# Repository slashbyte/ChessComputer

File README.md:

# PI Chess Computer
Modeled after the "Chess Challenger" made in 1978.
This PI powered, retro themed build,
is an open source hardware design capable of running an up to date chess engine, Stockfish.

## Raspberry PI Image Release
[Chess Challenger PI Image](https://github.com/slashbyte/ChessComputer-Source/releases)

### Computer Chess Clubs, BEWARE!
(Thats still a thing, right?)

## Authors
* **Slash/Byte** (slashqpbyte@gmail.com)
## License
This project is licensed under the MIT License
(https://opensource.org/licenses/MIT)
## Acknowledgments
* Science
* Adafruit
* Ponoko (Great fab house)
* Digikey

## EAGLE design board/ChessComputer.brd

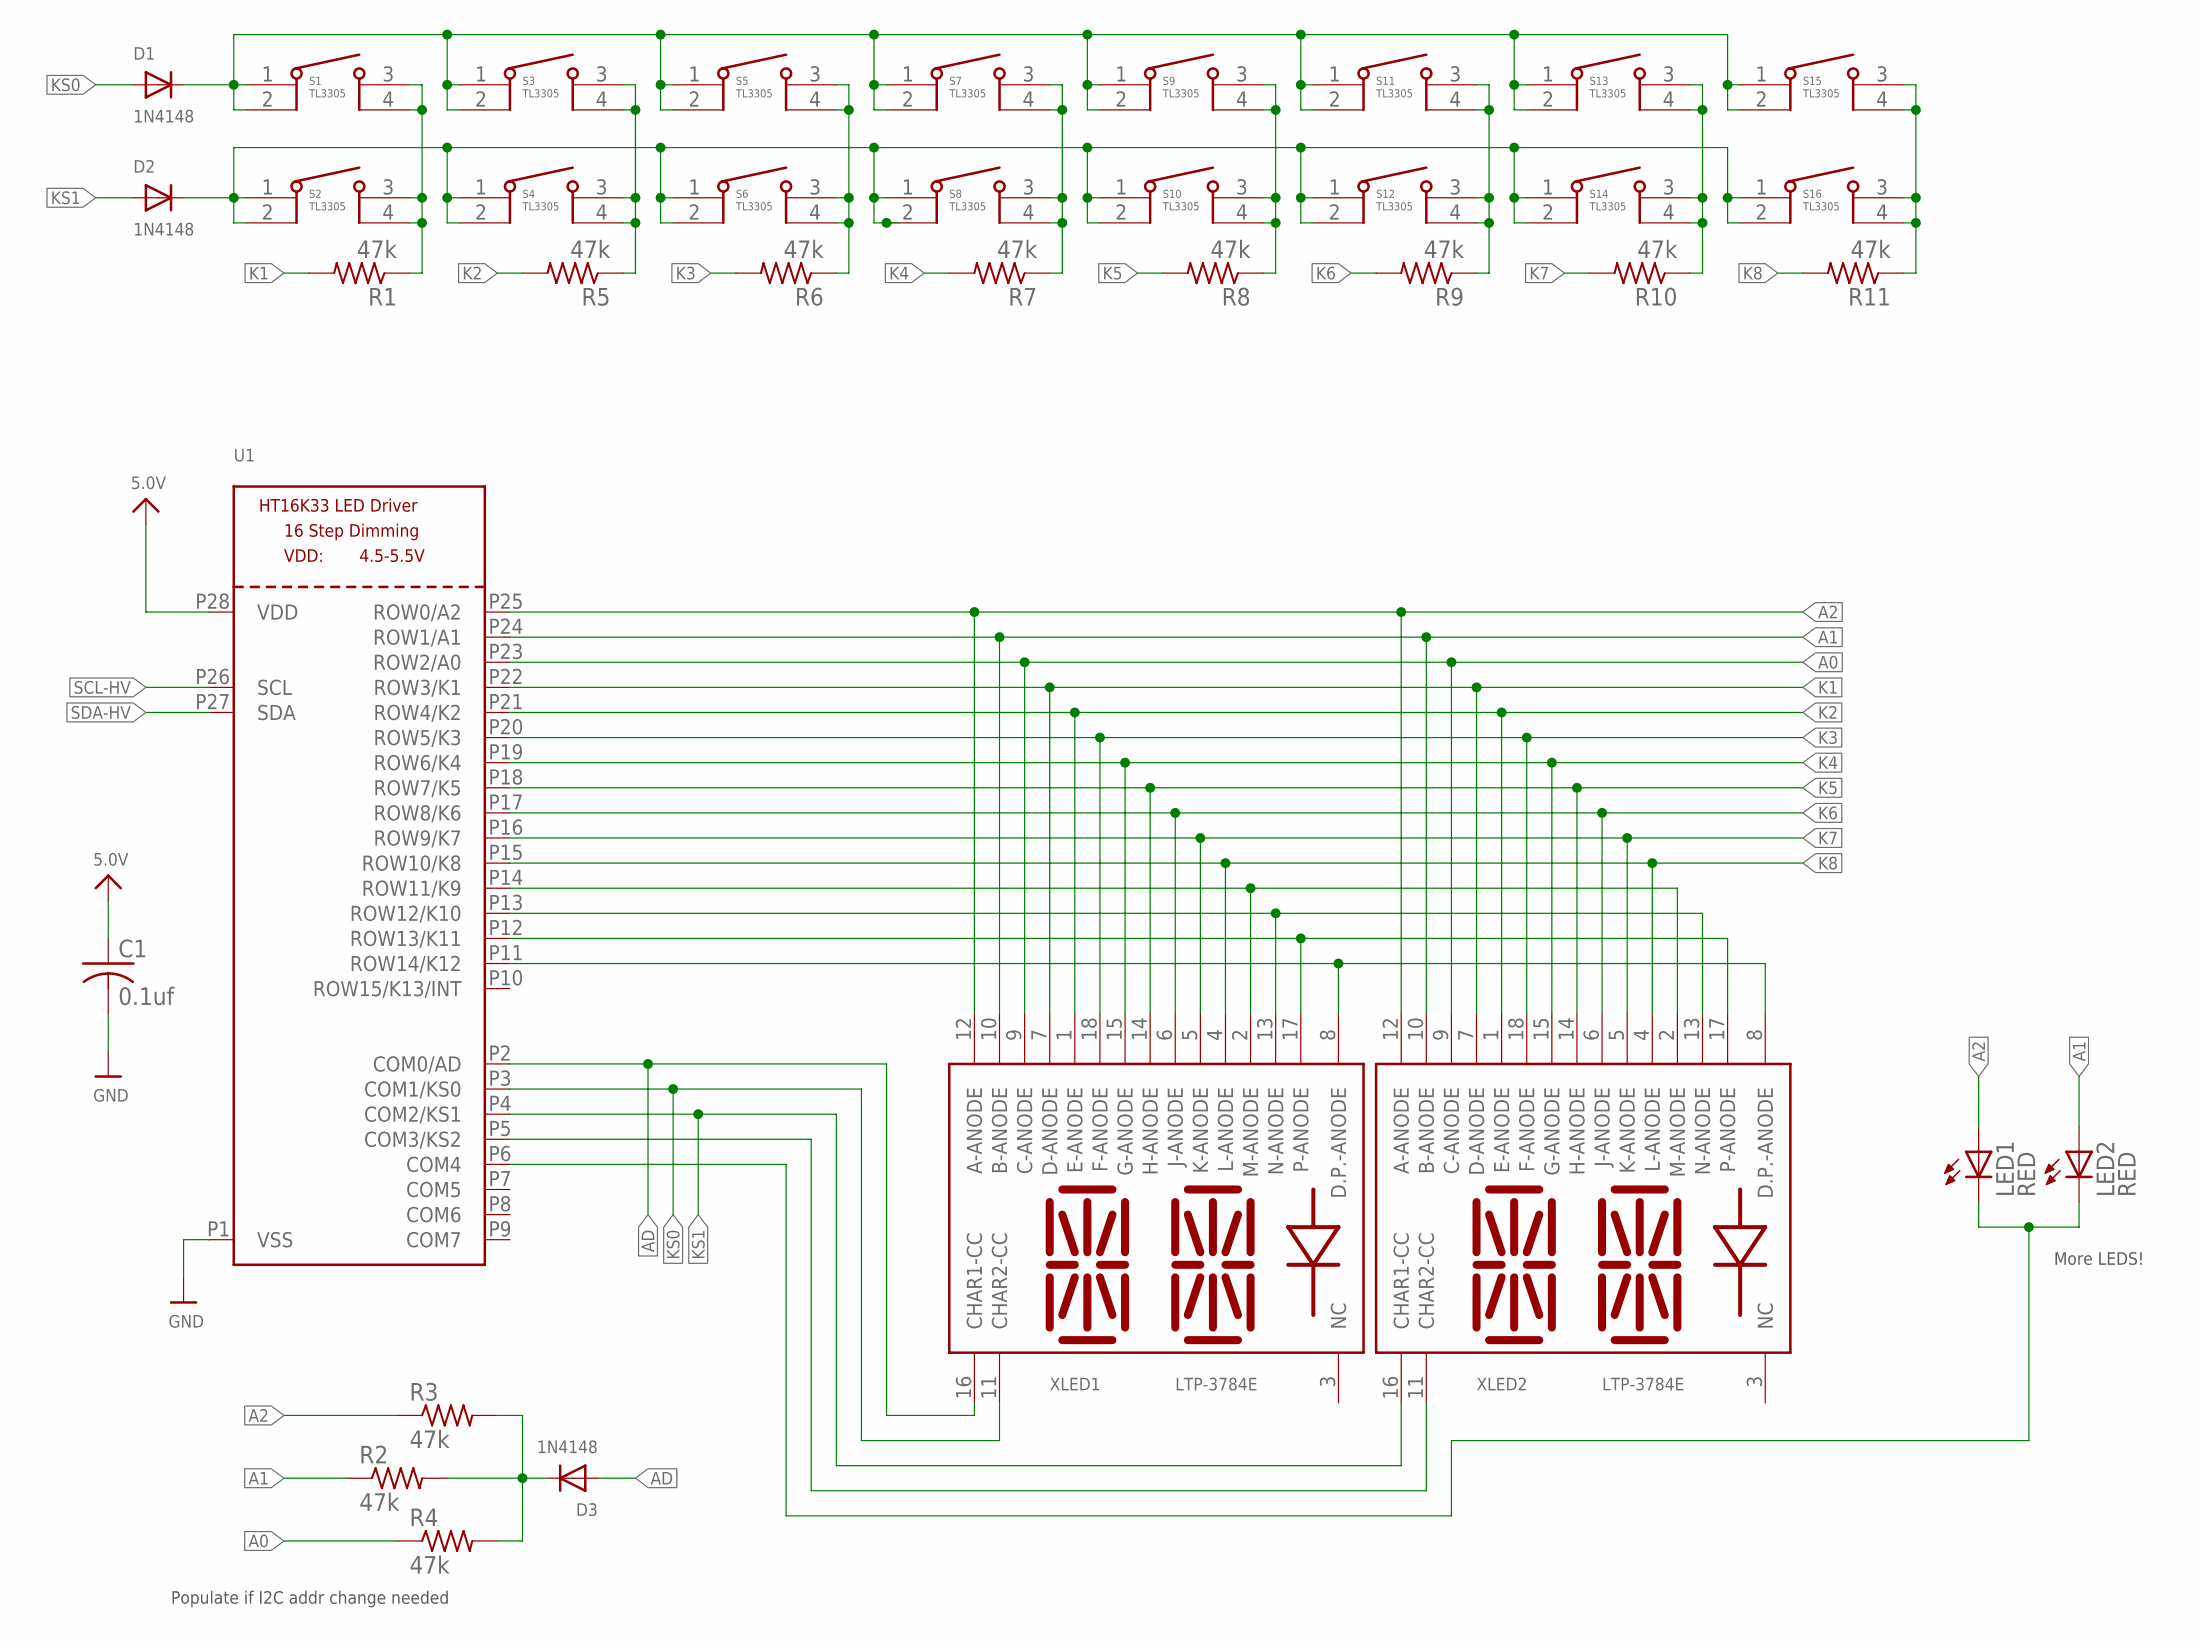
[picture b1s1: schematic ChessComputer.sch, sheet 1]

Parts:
C1: 0.1uf; C0805K
D1, D2, D3: 1N4148; SOD-523
LED1, LED2: RED; LED3MM
R1, R2, R3, R4, R5, R6, R7, R8, R9, R10, R11: 47k; M0805
S1, S2, S3, S4, S5, S6, S7, S8, S9, S10, S11, S12, S13, S14, S15, S16: TL3305
U1: HT16K33_SOP28; SOP28_300MIL
XLED1, XLED2: LTP-3784E; TLP-3784E

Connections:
5.0V: C1.1, U1.P28 (VDD); also elsewhere on the board
A0: R4.1, U1.P23 (ROW2/A0), XLED1.9 (C-ANODE), XLED2.9 (C-ANODE)
A1: LED2.A, R2.1, U1.P24 (ROW1/A1), XLED1.10 (B-ANODE), XLED2.10 (B-ANODE)
A2: LED1.A, R3.1, U1.P25 (ROW0/A2), XLED1.12 (A-ANODE), XLED2.12 (A-ANODE)
AD: D3.A, U1.P2 (COM0/AD), XLED1.16 (CHAR1-CC)
GND: C1.2, U1.P1 (VSS); also elsewhere on the board
K1: R1.2, U1.P22 (ROW3/K1), XLED1.7 (D-ANODE), XLED2.7 (D-ANODE)
K2: R5.2, U1.P21 (ROW4/K2), XLED1.1 (E-ANODE), XLED2.1 (E-ANODE)
K3: R6.2, U1.P20 (ROW5/K3), XLED1.18 (F-ANODE), XLED2.18 (F-ANODE)
K4: R7.2, U1.P19 (ROW6/K4), XLED1.15 (G-ANODE), XLED2.15 (G-ANODE)
K5: R8.2, U1.P18 (ROW7/K5), XLED1.14 (H-ANODE), XLED2.14 (H-ANODE)
K6: R9.2, U1.P17 (ROW8/K6), XLED1.6 (J-ANODE), XLED2.6 (J-ANODE)
K7: R10.2, U1.P16 (ROW9/K7), XLED1.5 (K-ANODE), XLED2.5 (K-ANODE)
K8: R11.2, U1.P15 (ROW10/K8), XLED1.4 (L-ANODE), XLED2.4 (L-ANODE)
KS0: D1.A, U1.P3 (COM1/KS0), XLED1.11 (CHAR2-CC)
KS1: D2.A, U1.P4 (COM2/KS1), XLED2.16 (CHAR1-CC)
unnamed: LED1.K (C), LED2.K (C), U1.P6 (COM4)
unnamed: U1.P14 (ROW11/K9), XLED1.2 (M-ANODE), XLED2.2 (M-ANODE)
unnamed: U1.P13 (ROW12/K10), XLED1.13 (N-ANODE), XLED2.13 (N-ANODE)
unnamed: U1.P12 (ROW13/K11), XLED1.17 (P-ANODE), XLED2.17 (P-ANODE)
unnamed: U1.P11 (ROW14/K12), XLED1.8 (D.P.-ANODE), XLED2.8 (D.P.-ANODE)
unnamed: D2.K (C), S2.1, S2.2, S4.1, S4.2, S6.1, S6.2, S8.1, S8.2, S10.1, S10.2, S12.1, S12.2, S14.1, S14.2, S16.1, S16.2
unnamed: U1.P5 (COM3/KS2), XLED2.11 (CHAR2-CC)
unnamed: D3.K (C), R2.2, R3.2, R4.2
unnamed: R1.1, S1.3, S1.4, S2.3, S2.4
unnamed: R5.1, S3.3, S3.4, S4.3, S4.4
unnamed: R6.1, S5.3, S5.4, S6.3, S6.4
unnamed: R7.1, S7.3, S7.4, S8.3, S8.4
unnamed: R8.1, S9.3, S9.4, S10.3, S10.4
unnamed: R9.1, S11.3, S11.4, S12.3, S12.4
unnamed: D1.K (C), S1.1, S1.2, S3.1, S3.2, S5.1, S5.2, S7.1, S7.2, S9.1, S9.2, S11.1, S11.2, S13.1, S13.2, S15.1, S15.2
unnamed: R10.1, S13.3, S13.4, S14.3, S14.4
unnamed: R11.1, S15.3, S15.4, S16.3, S16.4
SCL-HV: U1.P26 (SCL); also elsewhere on the board
SDA-HV: U1.P27 (SDA); also elsewhere on the board

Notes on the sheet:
More LEDS!
Populate if I2C addr change needed

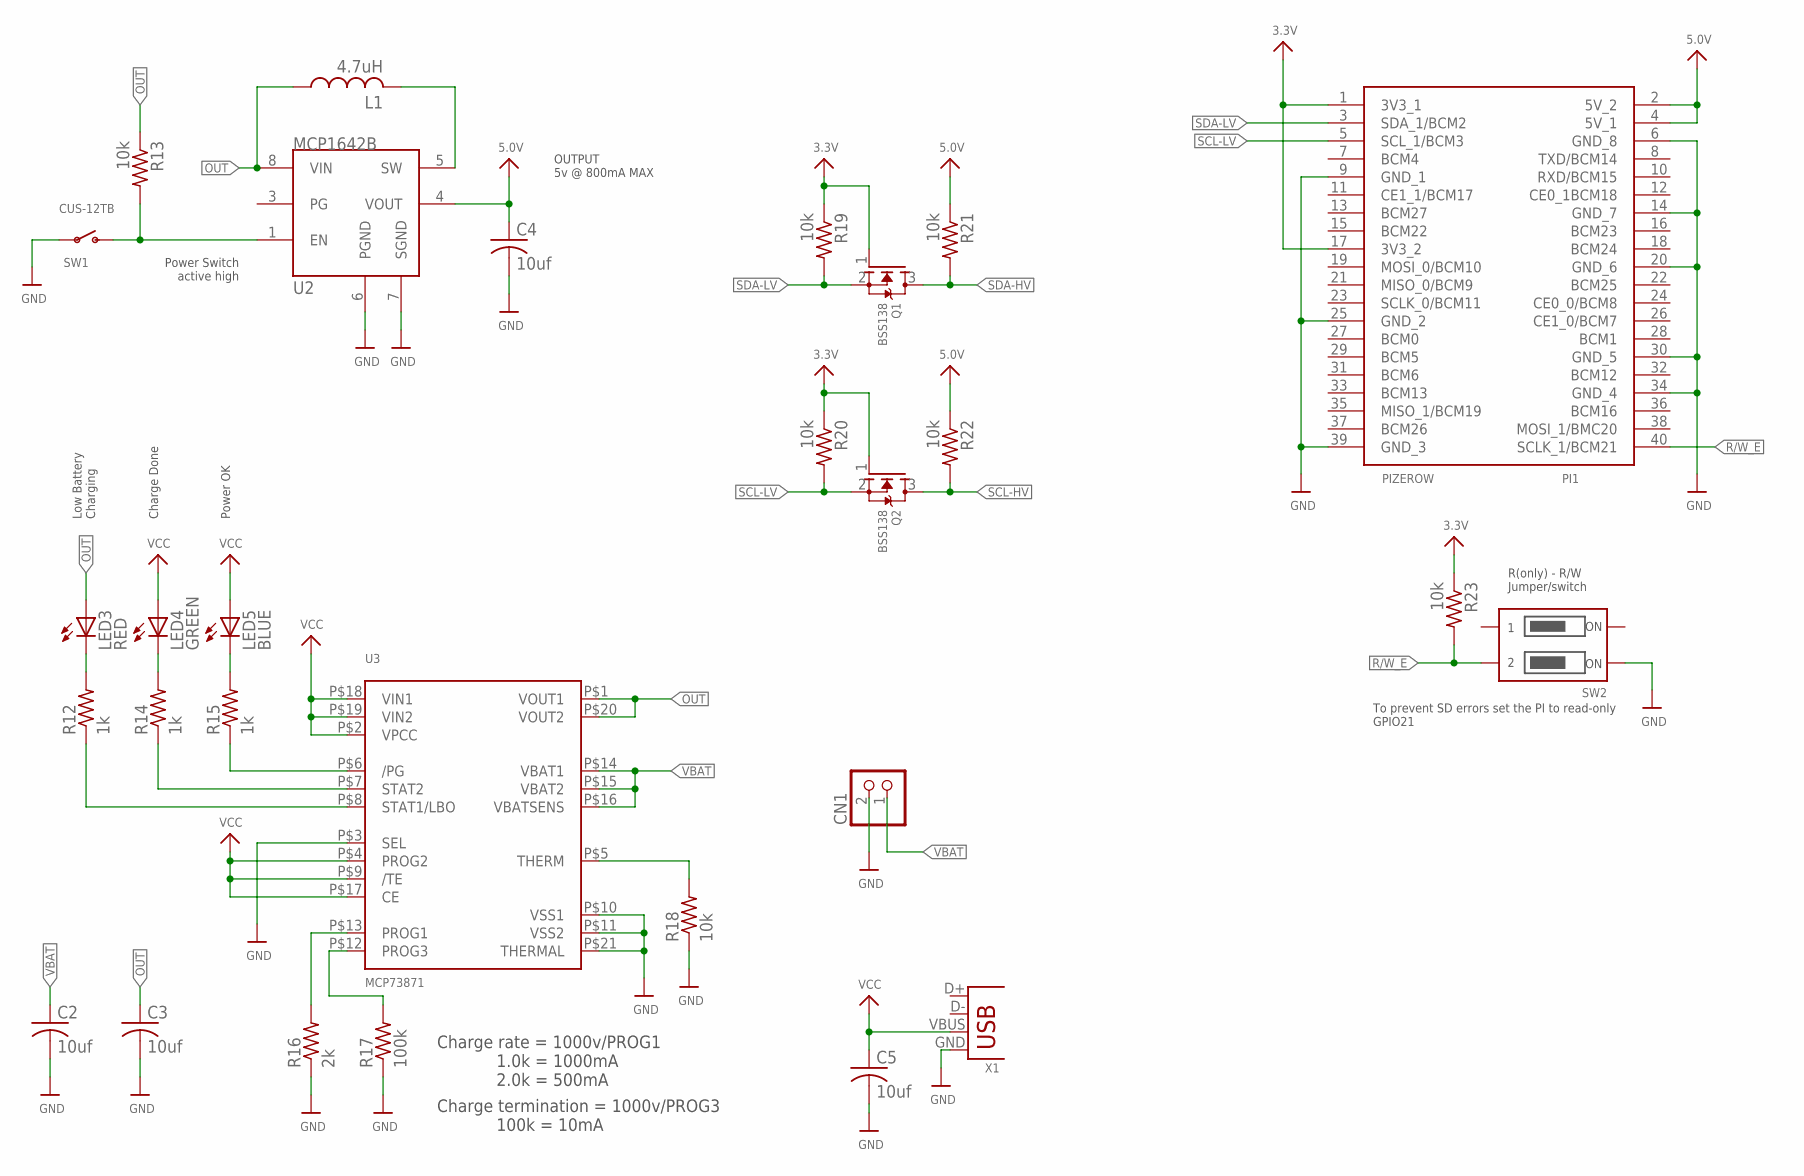
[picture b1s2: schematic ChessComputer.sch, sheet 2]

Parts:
C2, C3, C4, C5: 10uf; C0805K
CN1: JST_2PIN-SMT-RA; JST-PH-2-SMT-RA
L1: 4.7uH; TYS60204R7N-10
LED3: RED; LED3MM
LED4: GREEN; LED3MM
LED5: BLUE; LED3MM
PI1: PIZEROW; RASP_PI_ZERO_BOARD_FULL
Q1, Q2: BSS138; SOT23-R
R12, R14, R15: 1k; M0805
R13, R18, R19, R20, R21, R22, R23: 10k; M0805
R16: 2k; M0805
R17: 100k; M0805
SW1: CUS-12TB; SPST_SMT_19192
SW2: DIPSWITCH_2PIN
U2: MCP1642B; MSOP8
U3: MCP73871; QFN20_4MM
X1: MICRO-USB_ORIG; DX4R005HJ5

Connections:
3.3V: PI1.1 (3V3_1), PI1.17 (3V3_2), Q1.1 (G), Q2.1 (G), R19.1, R20.1, R23.1
5.0V: C4.1, PI1.2 (5V_2), PI1.4 (5V_1), R21.1, R22.1, U2.4 (VOUT); also elsewhere on the board
ENABLE: R13.2, SW1.C (S), U2.1 (EN)
GND: C2.2, C3.2, C4.2, C5.2, CN1.2 (1), PI1.6 (GND_8), PI1.9 (GND_1), PI1.14 (GND_7), PI1.20 (GND_6), PI1.25 (GND_2), PI1.30 (GND_5), PI1.34 (GND_4), PI1.39 (GND_3), R16.1, R17.1, R18.1, SW1.B, SW2.1A, U2.6 (PGND), U2.7 (SGND), U3.P$3 (SEL), U3.P$10 (VSS1), U3.P$11 (VSS2), U3.P$21 (THERMAL), X1.GND; also elsewhere on the board
unnamed: R18.2, U3.P$5 (THERM)
unnamed: R17.2, U3.P$12 (PROG3)
unnamed: R16.2, U3.P$13 (PROG1)
unnamed: L1.P$2 (2), U2.5 (SW)
unnamed: R15.1, U3.P$6 (/PG)
unnamed: LED5.K (C), R15.2
unnamed: LED4.K (C), R14.2
unnamed: LED3.K (C), R12.2
unnamed: R14.1, U3.P$7 (STAT2)
unnamed: R12.1, U3.P$8 (STAT1/LBO)
OUT: C3.1, L1.P$1 (1), LED3.A, R13.1, U2.8 (VIN), U3.P$1 (VOUT1), U3.P$20 (VOUT2)
R/W_E: PI1.40 (SCLK_1/BCM21), R23.2, SW2.1B
SCL-HV: Q2.3 (D), R22.2; also elsewhere on the board
SCL-LV: PI1.5 (SCL_1/BCM3), Q2.2 (S), R20.2
SDA-HV: Q1.3 (D), R21.2; also elsewhere on the board
SDA-LV: PI1.3 (SDA_1/BCM2), Q1.2 (S), R19.2
VBAT: C2.1, CN1.1 (2), U3.P$14 (VBAT1), U3.P$15 (VBAT2), U3.P$16 (VBATSENS)
VCC: C5.1, LED4.A, LED5.A, U3.P$2 (VPCC), U3.P$4 (PROG2), U3.P$9 (/TE), U3.P$17 (CE), U3.P$18 (VIN1), U3.P$19 (VIN2), X1.VBUS

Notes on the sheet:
Charge rate = 1000v/PROG1 1.0k = 1000mA 2.0k = 500mA
Charge termination = 1000v/PROG3 100k = 10mA
Low Battery Charging
Charge Done
Power OK
Power Switch active high
OUTPUT 5v @ 800mA MAX
R(only) - R/W Jumper/switch
To prevent SD errors set the PI to read-only GPIO21

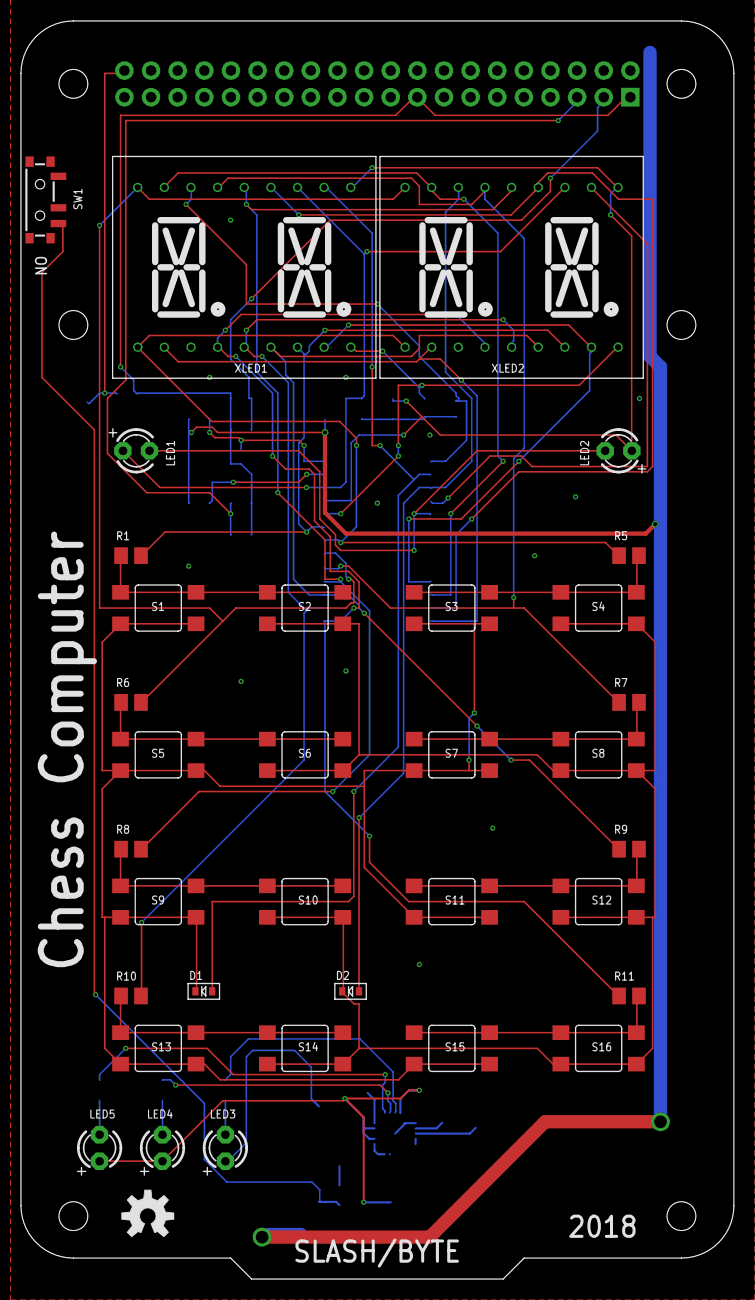
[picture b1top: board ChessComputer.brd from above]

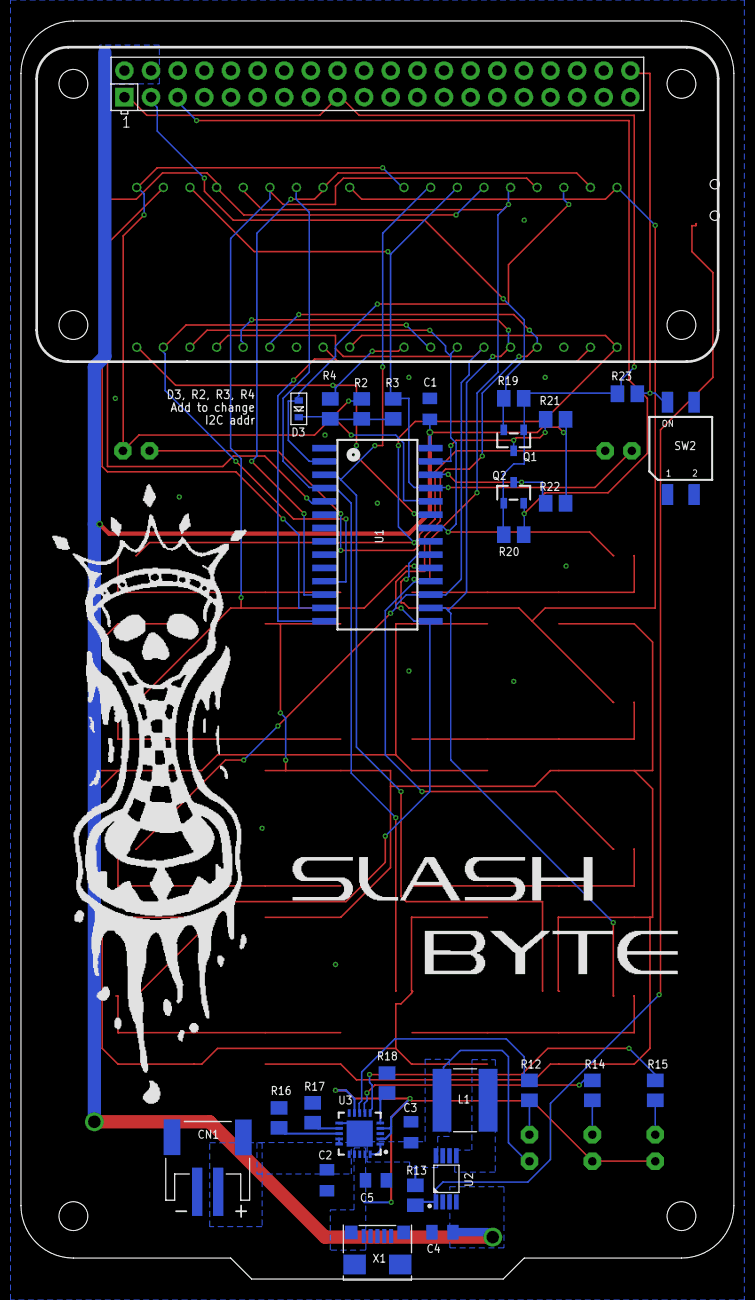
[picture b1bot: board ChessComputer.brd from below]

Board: 2 copper layers, 68.0 x 120.0 mm, 68 parts (33 on the bottom side), 53 nets.

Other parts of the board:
U$1: OSHW-LOGO-M
U$2: CHESSLOGO1
U$3: SLASHBYTE

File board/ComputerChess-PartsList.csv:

Qty,Value,Device,Package,Parts,Description,Digikey Part Number
1,,HT16K33_SOP28,SOP28_300MIL,U1,,
1,,DIPSWITCH_2PIN,DIPSWITCH_2PIN,SW2,DIP Switch - 2 Pin,732-6955-1-ND
1,,JST_2PIN-SMT-RA,JST-PH-2-SMT-RA,CN1,JST 2-Pin Connectors of various flavors,455-1749-1-ND
1,,MICRO-USB_ORIG,DX4R005HJ5,X1,SMD micro USB connector,670-2674-1-ND
1,0.1uf,C-USC0805K,C0805K,C1,"CAPACITOR, American symbol",732-8026-1-ND
1,100k,R-US_M0805,M0805,R17,"RESISTOR, American symbol",311-100KCRCT-ND
7,10k,R-US_M0805,M0805,"R13, R18, R19, R20, R21, R22, R23","RESISTOR, American symbol",A126332CT-ND
4,10uf,C-USC0805K,C0805K,"C2, C3, C4, C5","CAPACITOR, American symbol",732-7620-1-ND
3,1N4148,DIODESOD-523,SOD-523,"D1, D2, D3",Diode,1N4148XTPMSCT-ND
3,1k,R-US_M0805,M0805,"R12, R14, R15","RESISTOR, American symbol",A106056CT-ND
1,2k,R-US_M0805,M0805,R16,"RESISTOR, American symbol",311-2.00KCRCT-ND
1,4.7uH,TYS60204R7N-10,TYS60204R7N-10,L1,INDUCTOR,240-2724-1-ND
11,47k,R-US_M0805,M0805,"R1, R2, R3, R4, R5, R6, R7, R8, R9, R10, R11","RESISTOR, American symbol",311-47.0KCRCT-ND
1,BLUE,LED3MM,LED3MM,LED5,LED,732-5011-ND
2,BSS138,MOSFET-NREFLOW,SOT23-R,"Q1, Q2",N-Channel Mosfet,BSS138-FDICT-ND
1,CUS-12TB,SWITCH_SPST,SPST_SMT_19192,SW1,Switch - SPST,563-1102-1-ND
1,GREEN,LED3MM,LED3MM,LED4,LED,732-5012-ND
2,LTP-3784E,LTP-3784E,TLP-3784E,"XLED1, XLED2",Starburst Display x2,160-1010-ND
1,MCP1642B,MCP1642B,MSOP8,U2,MCP1642B,MCP1642B-50I/MS-ND
1,MCP73871,MCP73871,QFN20_4MM,U3,MCP73871 Lithium Polymer Battery Charger,MCP73871-2AAI/ML-ND
1,PIZEROW,PIZEROW,RASP_PI_ZERO_BOARD_FULL,PI1,40pin Header,609-4925-ND
3,RED,LED3MM,LED3MM,"LED1, LED2, LED3",LED,732-5013-ND
16,TL3305,TL3305,TL3305,"S1, S2, S3, S4, S5, S6, S7, S8, S9, S10, S11, S12, S13, S14, S15, S16",Switch (5mm board height),EG5354CT-ND

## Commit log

2018-11-20 added some stuff
    work in progress
2018-11-20 no comment
2018-11-23 case design
    kablam!
2018-11-23 text fix
    converted "text objects" to "path", whatever the hell that means.
2018-11-26 early test code
    limited hardware, concept testing. buggy as shit!
2018-11-26 tabs
    formating sucks...
2018-11-27 take 2
    rewrite?
2018-11-27 format
    formating
2018-11-28 still working on it
    trying to get something useable....
2018-11-28 still working
    how now brown cow!
2018-11-28 still working on it
    added stuff
2018-11-28 yep
    mhmm
2018-11-29 made changes
    umm... works better now
2018-11-30 fixed check led
    DP was being overwriten or something, idk, it was buggin me.
2018-11-30 moved to a repo
2018-12-02 assembly exploded
    added an exploded assembly guide
2018-12-08 pics
    lacking hardware, no more!
2018-12-09 new image

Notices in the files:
parts and their libraries:
microbuilder: This work is placed in the public domain, and may be freely used for commercial and non-commercial work with the following conditions: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
SparkFun-Aesthetics: Licensing: Creative Commons ShareAlike 4.0 International - https://creativecommons.org/licenses/by-sa/4.0
